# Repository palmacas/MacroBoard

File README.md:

# MacroBoard

MacroBoard is a 9-key hot-swappable mechanical macropad powered by [Seeed Studio XIAO RP2040](https://www.seeedstudio.com/XIAO-RP2040-v1-0-p-5026.html). The keyboard has 9 Kailh hot-swappable sockets compatible with any 3-pin or 5-pin MX switch, giving you the ability to choose the switches that suit you best. The keyboard also includes a rotary encoder with a push button and each key is backlit with an RGB LED.

## Features

- Uses Seeed XIAO RP2040, a small form factor board based on the Raspberry Pi RP2040 microcontroller.
- Supports MicroPython and CircuitPython.
- Kailh hot-swappable sockets compatible with 3-pin and 5-pin MX switches.
- Rotary quadrature encoder with push button.
- SK6812 reverse-mounted addressable RGB LEDs to backlight each key.
- Power and communication through a USB-C type port.
- Compatible with KMK keyboard firmware.
- Compatible with Windows, macOS, and Linux operating systems.
- Dimensions: 61mm x 81mm x 31mm (without case), 66mm x 86mm x 35mm (with 3D-printed case).

## Hardware Overview

## Getting Started

To set up the keyboard to work with CircuitPython and KMK Firmware, follow these steps:

### CircuitPython Installation

1. Enter Bootloader Mode
   - Press and hold the "BOOT" button.
   - Connect the Seeed XIAO RP2040 to your computer while still holding the button.
   - Your computer should now show a new drive, RPI-RP2.
2. Download the [firmware](https://circuitpython.org/board/seeeduino_xiao_rp2040/) for Seeed Studio XIAO RP2040.
3. Drag the .uf2 file to the drive RPI-RP2.
4. Check the drive. The name should now have changed to CIRCUITPY.

### NeoPixel Support 

5. Download the file [*neopixel.py*](https://github.com/adafruit/Adafruit_CircuitPython_NeoPixel/blob/main/neopixel.py) and copy it to the root directory on drive CIRCUITPY.

### KMK Installation

6. Download the [KMK Firmware](https://github.com/KMKfw/kmk_firmware) repository as a ZIP file.
7. Extract all files from de ZIP file and copy the *kmk* folder to the root directory on drive CIRCUITPY.
8. Download the files *code.py* and *boot.py* from the [firmware](firmware) folder.
9. Copy the files to the drive CIRCUITPY.
10. Restart the keyboard by pressing the "RESET" button or disconnecting and reconnecting to the computer.

### Keyboard Configuration

The key mapping defines the function and behavior of each key using a keycode or set of keycodes. The following code, which can be found in the file *code.py*, shows the key mapping for MacroBoard.

```python
# Keymap
keyboard.keymap = [
    [KC.LCTRL(KC.LSHIFT(KC.TAB)), KC.LCTRL(KC.M), KC.LCTRL(KC.TAB),
     KC.MEDIA_PREV_TRACK, KC.MEDIA_PLAY_PAUSE, KC.MEDIA_NEXT_TRACK,
     KC.LCTRL(KC.C), KC.LCTRL(KC.V), KC.LGUI(KC.SPACE),
    ]
]
```
In this example, the keys in the first row can switch between browser tabs and mute a tab. The keys in the second row can control the media player, and the keys in the third row function as `Ctrl+C`, `Ctrl+V`, and `GUI+SPACE`.

||COLUMN 1 |COLUMN 2 | COLUMN 3|
|---|---|---|---|
|ROW 1|CTRL+SHIFT+TAB |CTRL+M |CTRL+TAB |
|ROW 2|PREV TRACK |PLAY/PAUSE |NEXT TRACK |
|ROW 3|CTRL+C |CTRL+V |GUI+SPACE|

You can find a list of all available keycodes at the [KMK Firmware's](http://kmkfw.io/docs/keycodes) wiki.

## Disclaimer

The CircuitPython firmware, KMK Firmware, and NeoPixel library are managed and maintained by their respective developers.

---
More information:  
[MacroBoard – Design and Assembly](https://palmacas.com/macroboard-design/) [[Spanish]](https://palmacas.com/macroboard-diseno/)  
[MacroBoard – Configuration](https://palmacas.com/macroboard-configuration/) [[Spanish]](https://palmacas.com/macroboard-configuracion/)

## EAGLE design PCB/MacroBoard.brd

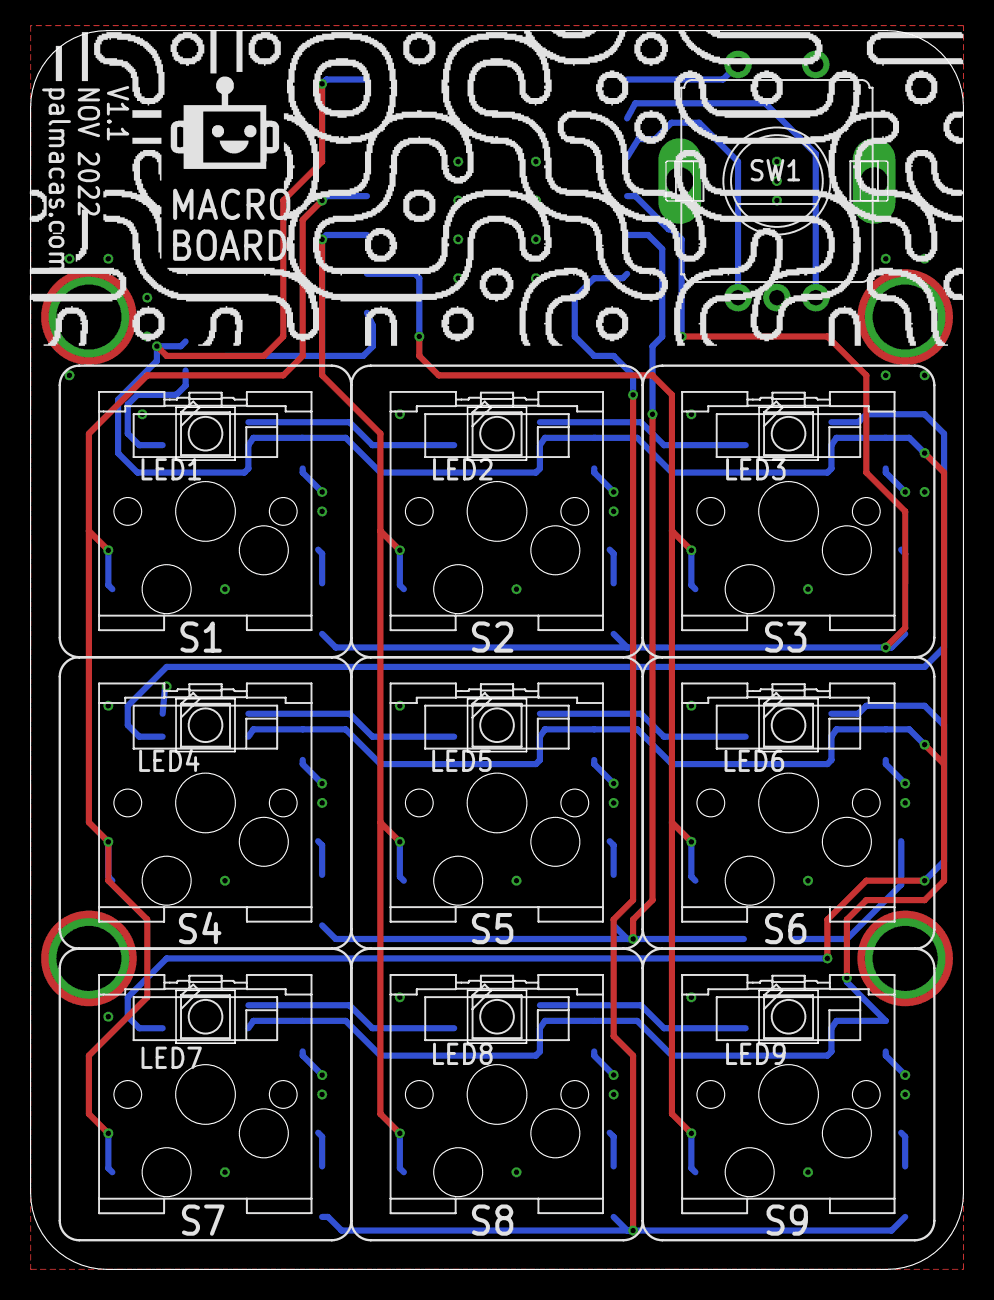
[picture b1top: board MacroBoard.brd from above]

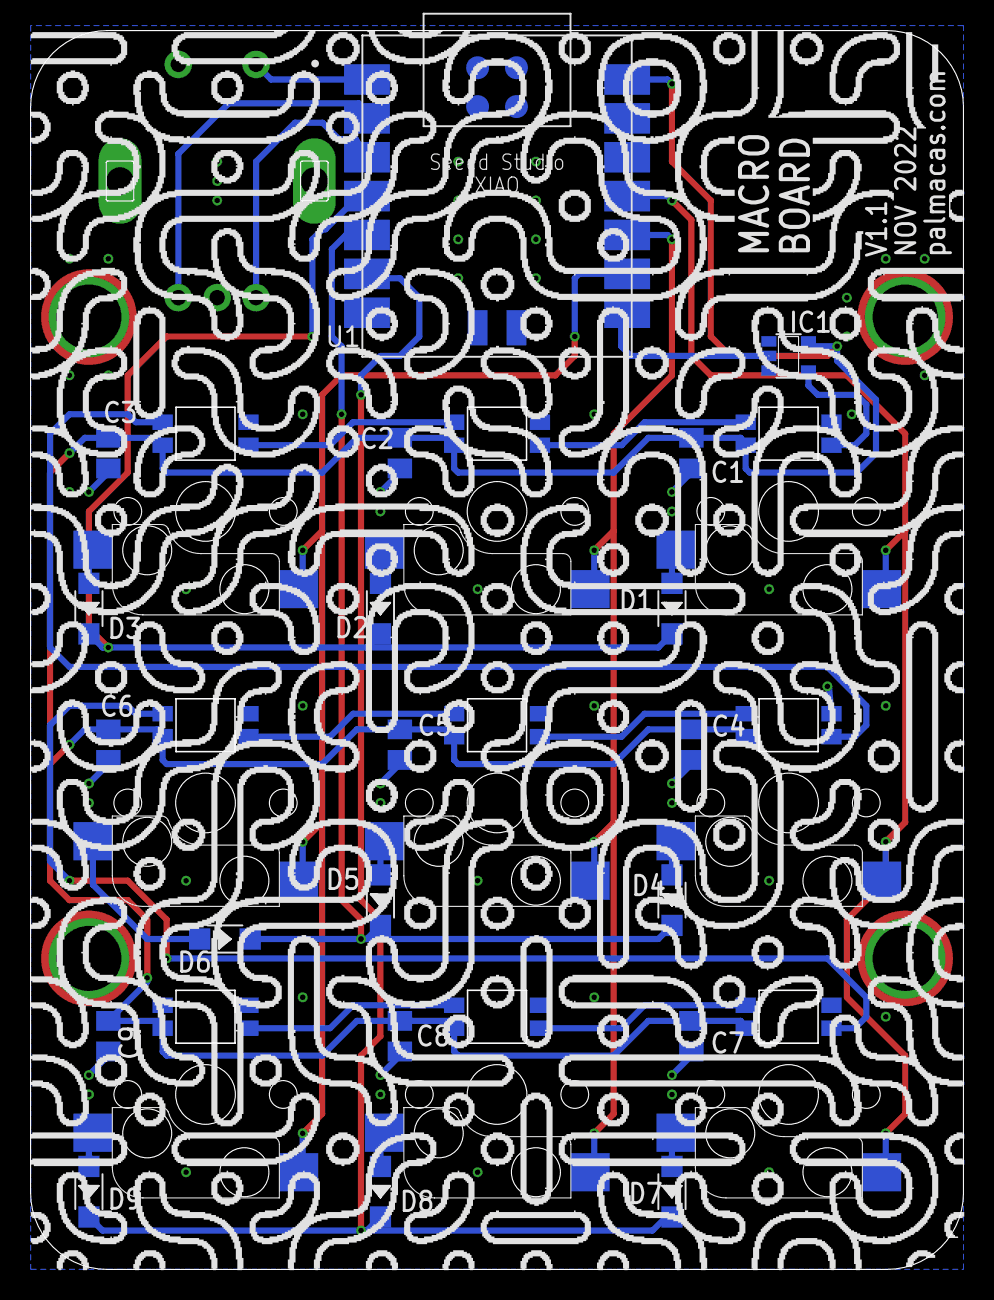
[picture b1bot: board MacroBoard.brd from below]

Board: 2 copper layers, 60.9 x 80.8 mm, 44 parts (20 on the bottom side), 30 nets.

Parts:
C1, C2, C3, C4, C5, C6, C7, C8, C9: 0.1uF; C0805K
D1, D2, D3, D4, D5, D6, D7, D8, D9: 1N4148W; SOD-123
IC1: 74AHC1G125DBV; SOT23-5
LED1, LED2, LED3, LED4, LED5, LED6, LED7, LED8, LED9: MICROBUILDER_WS2812B_SK6812E; MICROBUILDER_NEO3535_REVERSE
S1, S2, S3, S4, S5, S6, S7, S8, S9: SOCKET; ADAFRUIT_ELECTROMECH_KAILH_SOCKET
SW1: PEC11; ADAFRUIT_ELECTROMECH_PEC11+SWITCH
TP1, TP2, TP3, TP4: SEWTAP_SMTNUTM3; SMT_NUT_3MM
U1: SEEED-STUDIO-XIAO-SERIES_XIAO-RP2040; SEEED-STUDIO-XIAO-SERIES_XIAO-SAMD21/RP2040-MODULE14P-2.54-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
U$2: PALMACAS_AVATAR_BLACK#PNG

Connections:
+5V: C1.1, C2.1, C3.1, C4.1, C5.1, C6.1, C7.1, C8.1, C9.1, IC1.5, LED1.1-VDD, LED2.1-VDD, LED3.1-VDD, LED4.1-VDD, LED5.1-VDD, LED6.1-VDD, LED7.1-VDD, LED8.1-VDD, LED9.1-VDD, U1.14
BTN: SW1.P$1, U1.1
COL1: S1.1, S4.1, S7.1, U1.11
COL2: S2.1, S5.1, S8.1, U1.10
COL3: S3.1, S6.1, S9.1, U1.9
GND: C1.2, C2.2, C3.2, C4.2, C5.2, C6.2, C7.2, C8.2, C9.2, IC1.1, IC1.3, LED1.3-GND, LED2.3-GND, LED3.3-GND, LED4.3-GND, LED5.3-GND, LED6.3-GND, LED7.3-GND, LED8.3-GND, LED9.3-GND, SW1.P$2, SW1.P$C, SW1.P$GND1, SW1.P$GND2, TP1.P$1, TP2.P$1, TP3.P$1, TP4.P$1, U1.13, U1.18, U1.20
unnamed: LED8.2-DOUT, LED9.4-DIN
unnamed: LED7.2-DOUT, LED8.4-DIN
unnamed: LED5.2-DOUT, LED6.4-DIN
unnamed: LED6.2-DOUT, LED7.4-DIN
unnamed: LED4.2-DOUT, LED5.4-DIN
unnamed: LED3.2-DOUT, LED4.4-DIN
unnamed: LED1.2-DOUT, LED2.4-DIN
unnamed: LED2.2-DOUT, LED3.4-DIN
unnamed: IC1.4, LED1.4-DIN
unnamed: D1.+, S1.2
unnamed: D4.+, S4.2
unnamed: D7.+, S7.2
unnamed: D2.+, S2.2
unnamed: D5.+, S5.2
unnamed: D8.+, S8.2
unnamed: D3.+, S3.2
unnamed: D6.+, S6.2
unnamed: D9.+, S9.2
NEOPIXEL: IC1.2, U1.8
ROTA: SW1.P$A, U1.3
ROTB: SW1.P$B, U1.2
ROW1: D1.-, D2.-, D3.-, U1.4
ROW2: D4.-, D5.-, D6.-, U1.5
ROW3: D7.-, D8.-, D9.-, U1.6

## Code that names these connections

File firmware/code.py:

"""
MacroBoard

* Cristian Palma (palmacas)
"""

import board
from kmk.kmk_keyboard import KMKKeyboard
from kmk.keys import KC
from kmk.scanners import DiodeOrientation
from kmk.extensions.RGB import RGB, AnimationModes
from kmk.extensions.media_keys import MediaKeys
from kmk.modules.encoder import EncoderHandler

# Pinout
COL1 = board.D10
COL2 = board.D9
COL3 = board.D8
ROW1 = board.D3
ROW2 = board.D4
ROW3 = board.D5
PUSHBUTTON = board.D0
ROTA = board.D2
ROTB = board.D1
NEOPIXEL = board.D7

keyboard = KMKKeyboard()

# Basic matrix settings
keyboard.col_pins = (COL1, COL2, COL3)
keyboard.row_pins = (ROW1, ROW2, ROW3)
keyboard.diode_orientation = DiodeOrientation.COL2ROW

# RGB LEDs settings
rgb_ext = RGB( 
    pixel_pin = NEOPIXEL,
    num_pixels = 9,
    hue_default = 100,
    sat_default = 255,
    val_default = 15,
    val_limit = 25,
    animation_speed = 1,
    animation_mode=AnimationModes.RAINBOW,
    refresh_rate = 30,
)
keyboard.extensions.append(rgb_ext)
keyboard.extensions.append(MediaKeys())

# Encoder settings
encoder_handler = EncoderHandler()
keyboard.modules.append(encoder_handler)
encoder_handler.pins = ((ROTA, ROTB, PUSHBUTTON, False),)
encoder_handler.map = (((KC.VOLD, KC.VOLU, KC.MUTE),),)

# Keymap
keyboard.keymap = [
    [KC.LCTRL(KC.LSHIFT(KC.TAB)), KC.LCTRL(KC.M), KC.LCTRL(KC.TAB),
     KC.MEDIA_PREV_TRACK, KC.MEDIA_PLAY_PAUSE, KC.MEDIA_NEXT_TRACK,
     KC.LCTRL(KC.C), KC.LCTRL(KC.V), KC.LGUI(KC.SPACE),
    ]
]

if __name__ == '__main__':
    keyboard.go()

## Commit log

2023-01-12 V1.1 update
2024-11-13 Update README.md
    adding a hyperlink to the product for people who want to explore more
